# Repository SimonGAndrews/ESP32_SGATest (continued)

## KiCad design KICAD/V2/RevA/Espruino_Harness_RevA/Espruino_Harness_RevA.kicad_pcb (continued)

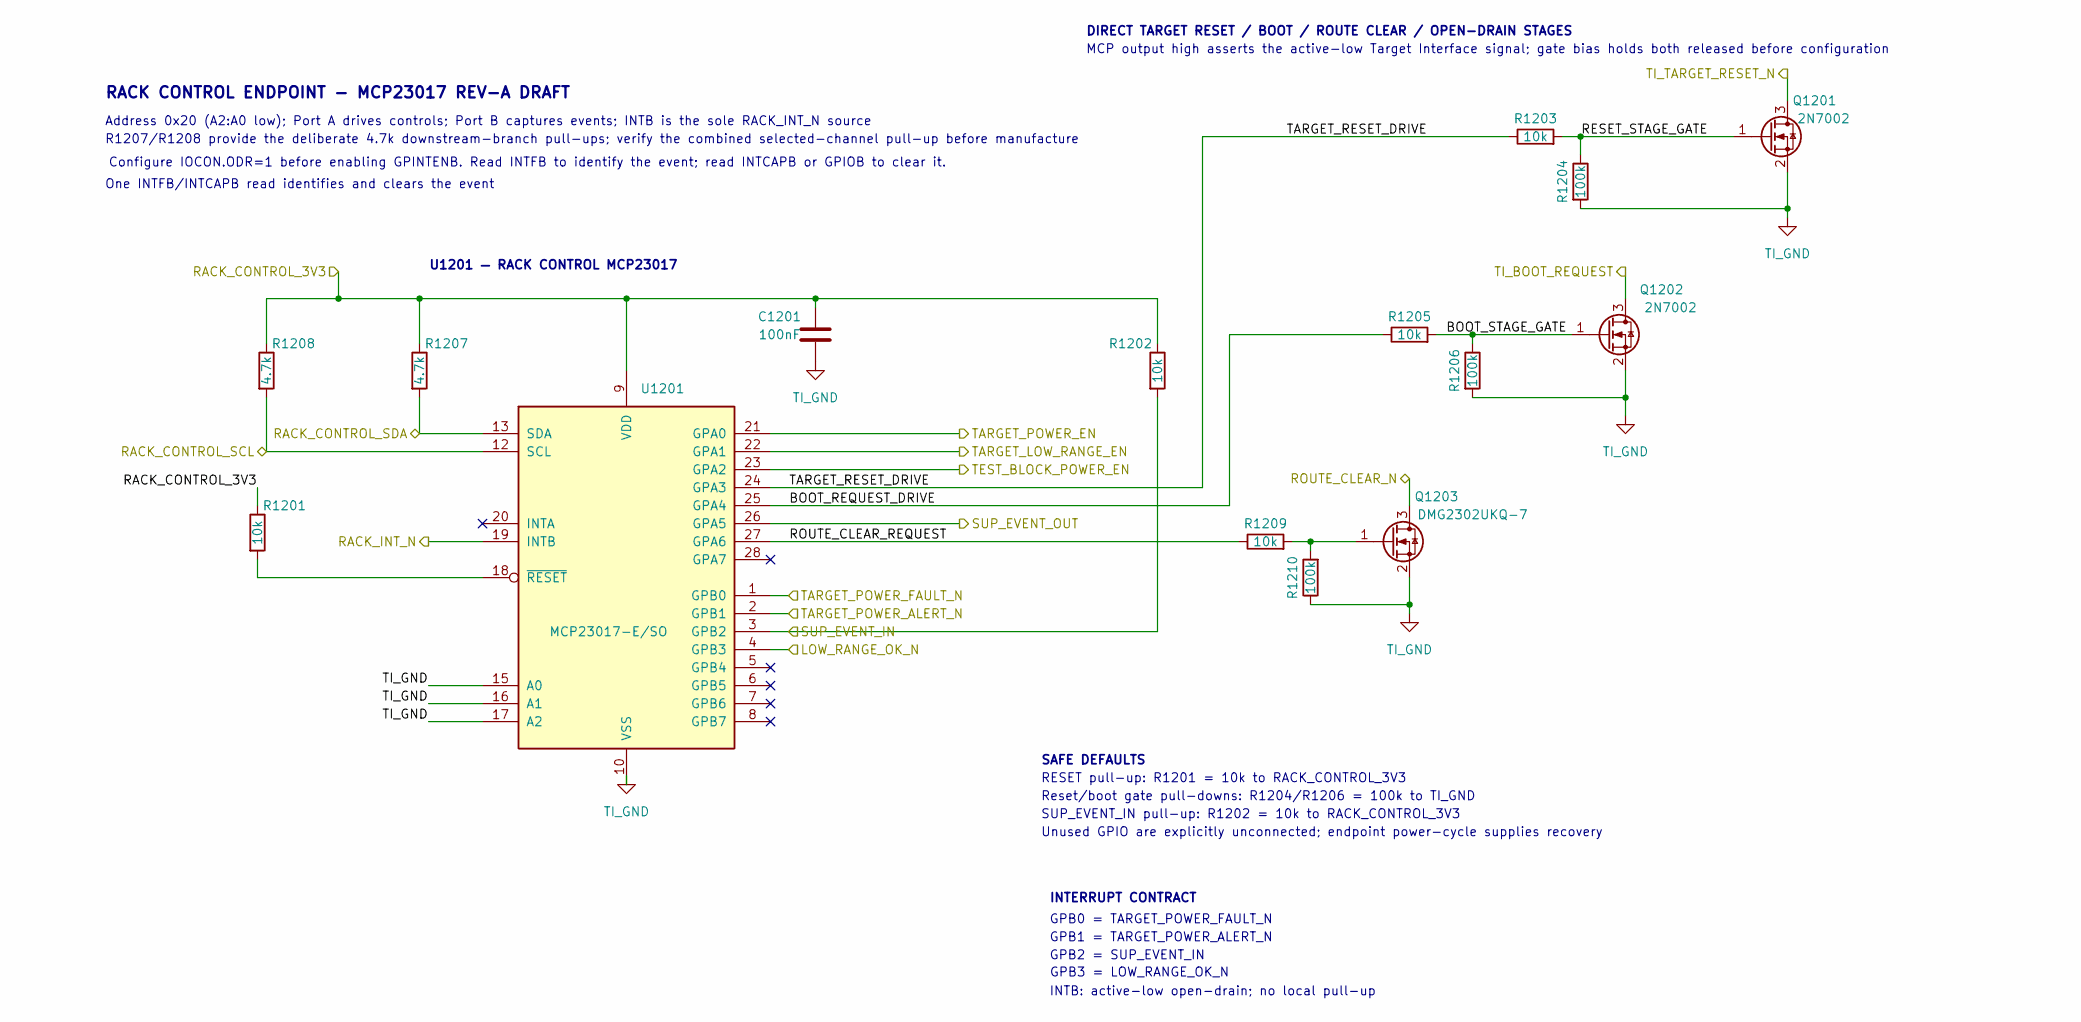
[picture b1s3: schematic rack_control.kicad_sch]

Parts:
C1201: 100nF; C_0603_1608Metric
Q1201, Q1202: 2N7002; SOT-23
Q1203: DMG2302UKQ-7; SOT-23; MPN DMG2302UKQ-7
R1201, R1202, R1203, R1205, R1209: 10k; R_0603_1608Metric
R1204, R1206, R1210: 100k; R_0603_1608Metric
R1207, R1208: 4.7k; R_0603_1608Metric
U1201: MCP23017-E/SO; SOIC-28W_7.5x17.9mm_P1.27mm

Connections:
/LOW_RANGE_OK_N: U1201.4 (GPB3); also elsewhere on the board
/RACK_CONTROL_3V3: C1201.1, R1201.1, R1202.1, R1207.1, R1208.1, U1201.9 (VDD); also elsewhere on the board
/RACK_CONTROL_SCL: R1208.2, U1201.12 (SCL); also elsewhere on the board
/RACK_CONTROL_SDA: R1207.2, U1201.13 (SDA); also elsewhere on the board
/RACK_INT_N: U1201.19 (INTB)
/ROUTE_CLEAR_N: Q1203.3 (D); also elsewhere on the board
/SUP_EVENT_IN: R1202.2, U1201.3 (GPB2); also elsewhere on the board
/SUP_EVENT_OUT: U1201.26 (GPA5); also elsewhere on the board
/TARGET_LOW_RANGE_EN: U1201.22 (GPA1); also elsewhere on the board
/TARGET_POWER_ALERT_N: U1201.2 (GPB1); also elsewhere on the board
/TARGET_POWER_EN: U1201.21 (GPA0); also elsewhere on the board
/TARGET_POWER_FAULT_N: U1201.1 (GPB0); also elsewhere on the board
/TEST_BLOCK_POWER_EN: U1201.23 (GPA2); also elsewhere on the board
/TI_BOOT_REQUEST: Q1202.3 (D); also elsewhere on the board
/TI_TARGET_RESET_N: Q1201.3 (D); also elsewhere on the board
/V2 Rev-A Rack Control Endpoint/BOOT_REQUEST_DRIVE: R1205.1, U1201.25 (GPA4)
/V2 Rev-A Rack Control Endpoint/BOOT_STAGE_GATE: Q1202.1 (G), R1205.2, R1206.1
/V2 Rev-A Rack Control Endpoint/RESET_STAGE_GATE: Q1201.1 (G), R1203.2, R1204.1
/V2 Rev-A Rack Control Endpoint/ROUTE_CLEAR_REQUEST: R1209.1, U1201.27 (GPA6)
/V2 Rev-A Rack Control Endpoint/TARGET_RESET_DRIVE: R1203.1, U1201.24 (GPA3)
unnamed: Q1203.1 (G), R1209.2, R1210.2
unnamed: R1201.2, U1201.18 (~RESET)
TI_GND: C1201.2, Q1201.2 (S), Q1202.2 (S), Q1203.2 (S), R1204.2, R1206.2, R1210.1, U1201.10 (VSS), U1201.15 (A0), U1201.16 (A1), U1201.17 (A2); also elsewhere on the board

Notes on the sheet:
GPB1 = TARGET_POWER_ALERT_N
MCP output high asserts the active-low Target Interface signal; gate bias holds both released before configuration
GPB2 = SUP_EVENT_IN
RACK CONTROL ENDPOINT - MCP23017 REV-A DRAFT
DIRECT TARGET RESET / BOOT / ROUTE CLEAR / OPEN-DRAIN STAGES
One INTFB/INTCAPB read identifies and clears the event
SAFE DEFAULTS
SUP_EVENT_IN pull-up: R1202 = 10k to RACK_CONTROL_3V3
Reset/boot gate pull-downs: R1204/R1206 = 100k to TI_GND
RESET pull-up: R1201 = 10k to RACK_CONTROL_3V3
GPB3 = LOW_RANGE_OK_N
INTB: active-low open-drain; no local pull-up
Unused GPIO are explicitly unconnected; endpoint power-cycle supplies recovery
GPB0 = TARGET_POWER_FAULT_N
Address 0x20 (A2:A0 low); Port A drives controls; Port B captures events; INTB is the sole RACK_INT_N source
R1207/R1208 provide the deliberate 4.7k downstream-branch pull-ups; verify the combined selected-channel pull-up before manufacture
U1201 — RACK CONTROL MCP23017
Configure IOCON.ODR=1 before enabling GPINTENB. Read INTFB to identify the event; read INTCAPB or GPIOB to clear it.
INTERRUPT CONTRACT

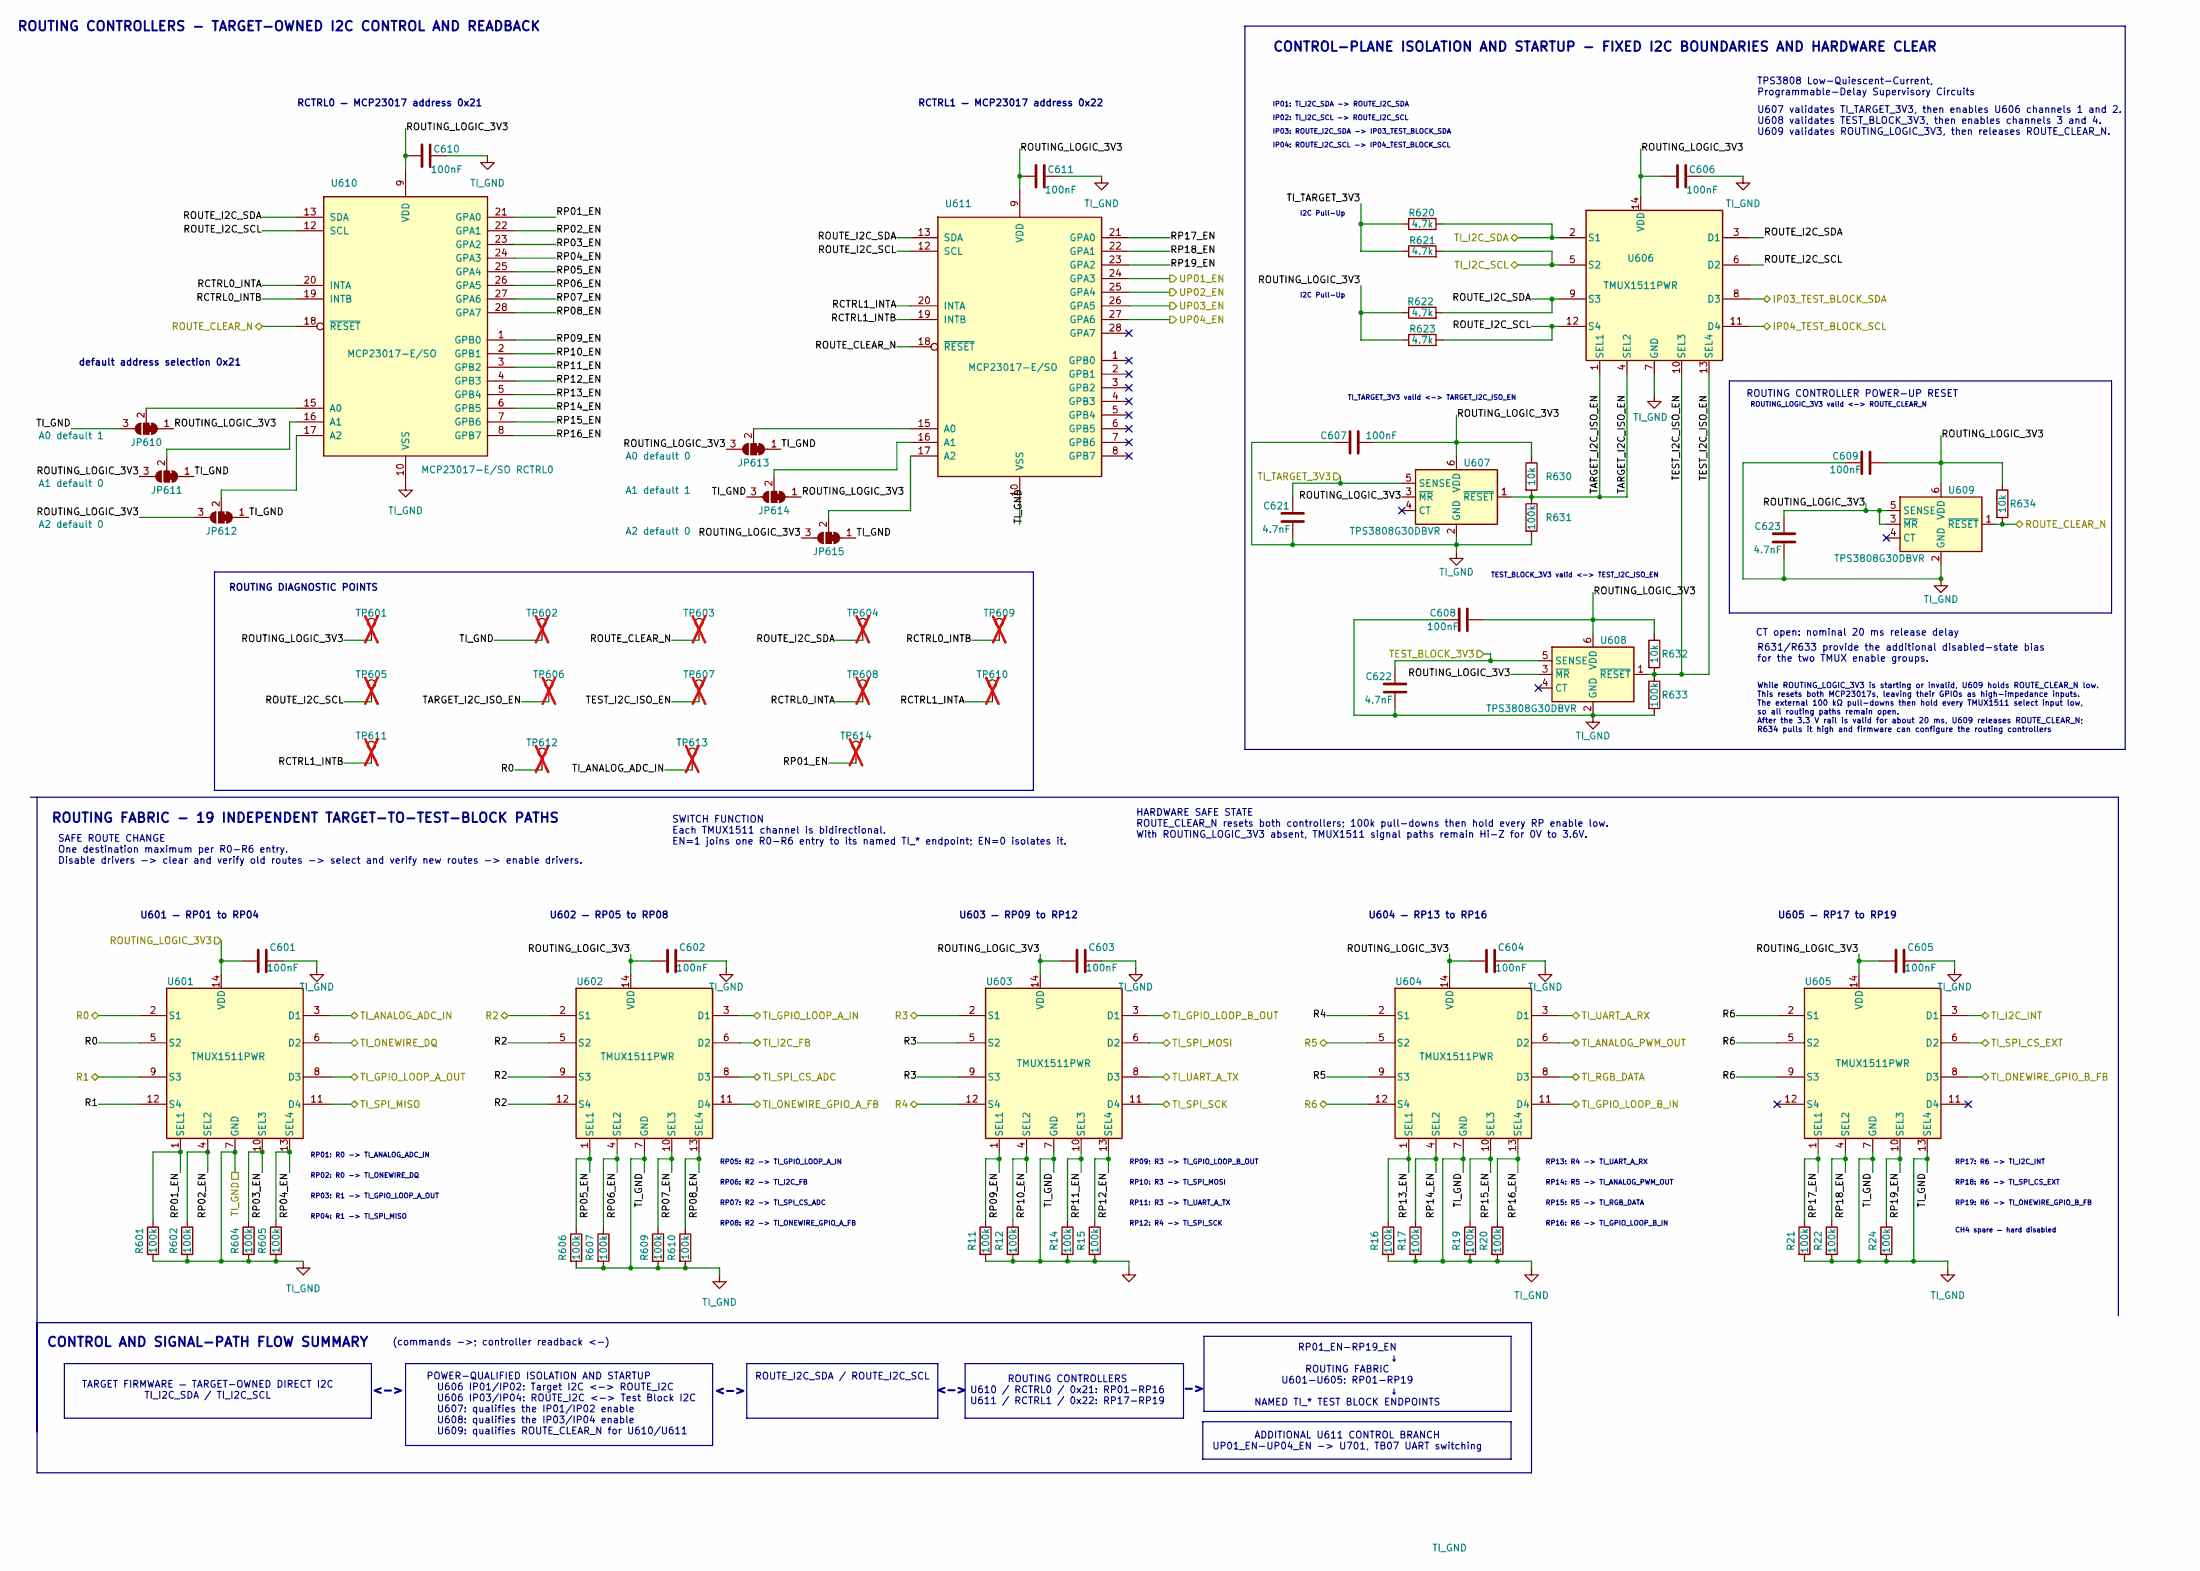
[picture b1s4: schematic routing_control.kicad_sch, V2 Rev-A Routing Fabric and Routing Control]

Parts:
C601, C602, C603, C604, C605, C606, C607, C608, C609, C610, C611: 100nF; C_0603_1608Metric
C621, C622, C623: 4.7nF; C_0603_1608Metric
JP610: A0 default 1; SolderJumper-3_P1.3mm_Bridged12_RoundedPad1.0x1.5mm_NumberL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
JP611: A1 default 0; SolderJumper-3_P1.3mm_Bridged12_RoundedPad1.0x1.5mm_NumberL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
JP612, JP615: A2 default 0; SolderJumper-3_P1.3mm_Bridged12_RoundedPad1.0x1.5mm_NumberL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
JP613: A0 default 0; SolderJumper-3_P1.3mm_Bridged12_RoundedPad1.0x1.5mm_NumberL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
JP614: A1 default 1; SolderJumper-3_P1.3mm_Bridged12_RoundedPad1.0x1.5mm_NumberL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
R11, R12, R14, R15, R16, R17, R19, R20, R21, R22, R24, R601, R602, R604, R605, R606, R607, R609, R610, R631, R633: 100k; R_0603_1608Metric
R620, R621, R622, R623: 4.7k; R_0603_1608Metric
R630, R632, R634: 10k; R_0603_1608Metric
TP601: ROUTING_LOGIC_3V3; PinHeader_1x01_P2.54mm_Vertical; MPN 61300111121; not fitted
TP602: TI_GND; PinHeader_1x01_P2.54mm_Vertical; MPN 61300111121; not fitted
TP603: ROUTE_CLEAR_N; PinHeader_1x01_P2.54mm_Vertical; MPN 61300111121; not fitted
TP604: ROUTE_I2C_SDA; PinHeader_1x01_P2.54mm_Vertical; MPN 61300111121; not fitted
TP605: ROUTE_I2C_SCL; PinHeader_1x01_P2.54mm_Vertical; MPN 61300111121; not fitted
TP606: TARGET_I2C_ISO_EN; PinHeader_1x01_P2.54mm_Vertical; MPN 61300111121; not fitted
TP607: TEST_I2C_ISO_EN; PinHeader_1x01_P2.54mm_Vertical; MPN 61300111121; not fitted
TP608: RCTRL0_INTA; PinHeader_1x01_P2.54mm_Vertical; MPN 61300111121; not fitted
TP609: RCTRL0_INTB; PinHeader_1x01_P2.54mm_Vertical; MPN 61300111121; not fitted
TP610: RCTRL1_INTA; PinHeader_1x01_P2.54mm_Vertical; MPN 61300111121; not fitted
TP611: RCTRL1_INTB; PinHeader_1x01_P2.54mm_Vertical; MPN 61300111121; not fitted
TP612: R0; PinHeader_1x01_P2.54mm_Vertical; MPN 61300111121; not fitted
TP613: TI_ANALOG_ADC_IN; PinHeader_1x01_P2.54mm_Vertical; MPN 61300111121; not fitted
TP614: RP01_EN; PinHeader_1x01_P2.54mm_Vertical; MPN 61300111121; not fitted
U601, U602, U603, U604, U605, U606: TMUX1511; TSSOP-14_4.4x5mm_P0.65mm; MPN TMUX1511PWR
U607, U608, U609: TPS3808G30DBVR; SOT-23-6; MPN TPS3808G30DBVR
U610: MCP23017-E/SO RCTRL0; SOIC-28W_7.5x17.9mm_P1.27mm; MPN MCP23017-E/SO
U611: MCP23017-E/SO RCTRL1; SOIC-28W_7.5x17.9mm_P1.27mm; MPN MCP23017-E/SO

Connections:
/IP03_TEST_BLOCK_SDA: U606.8 (D3); also elsewhere on the board
/IP04_TEST_BLOCK_SCL: U606.11 (D4); also elsewhere on the board
/R0: TP612.1, U601.2 (S1), U601.5 (S2); also elsewhere on the board
/R1: U601.9 (S3), U601.12 (S4); also elsewhere on the board
/R2: U602.2 (S1), U602.5 (S2), U602.9 (S3), U602.12 (S4); also elsewhere on the board
/R3: U603.2 (S1), U603.5 (S2), U603.9 (S3); also elsewhere on the board
/R4: U603.12 (S4), U604.2 (S1); also elsewhere on the board
/R5: U604.5 (S2), U604.9 (S3); also elsewhere on the board
/R6: U604.12 (S4), U605.2 (S1), U605.5 (S2), U605.9 (S3); also elsewhere on the board
/ROUTE_CLEAR_N: R634.2, TP603.1, U609.1 (~RESET), U610.18 (~RESET), U611.18 (~RESET); also elsewhere on the board
/ROUTING_LOGIC_3V3: C601.1, C602.1, C603.1, C604.1, C605.1, C606.1, C607.1, C608.1, C609.1, C610.1, C611.1, C623.1, JP610.1 (A), JP611.3 (B), JP612.3 (B), JP613.3 (B), JP614.1 (A), JP615.3 (B), R622.1, R623.1, R630.1, R632.1, R634.1, TP601.1, U601.14 (VDD), U602.14 (VDD), U603.14 (VDD), U604.14 (VDD), U605.14 (VDD), U606.14 (VDD), U607.3 (~MR), U607.6 (VDD), U608.3 (~MR), U608.6 (VDD), U609.3 (~MR), U609.5 (SENSE), U609.6 (VDD), U610.9 (VDD), U611.9 (VDD); also elsewhere on the board
/Routing_Control/RCTRL0_INTA: TP608.1, U610.20 (INTA)
/Routing_Control/RCTRL0_INTB: TP609.1, U610.19 (INTB)
/Routing_Control/RCTRL1_INTA: TP610.1, U611.20 (INTA)
/Routing_Control/RCTRL1_INTB: TP611.1, U611.19 (INTB)
/Routing_Control/ROUTE_I2C_SCL: R623.2, TP605.1, U606.6 (D2), U606.12 (S4), U610.12 (SCL), U611.12 (SCL)
/Routing_Control/ROUTE_I2C_SDA: R622.2, TP604.1, U606.3 (D1), U606.9 (S3), U610.13 (SDA), U611.13 (SDA)
/Routing_Control/RP01_EN: R601.1, TP614.1, U601.1 (SEL1), U610.21 (GPA0)
/Routing_Control/RP02_EN: R602.1, U601.4 (SEL2), U610.22 (GPA1)
/Routing_Control/RP03_EN: R604.1, U601.10 (SEL3), U610.23 (GPA2)
/Routing_Control/RP04_EN: R605.1, U601.13 (SEL4), U610.24 (GPA3)
/Routing_Control/RP05_EN: R606.1, U602.1 (SEL1), U610.25 (GPA4)
/Routing_Control/RP06_EN: R607.1, U602.4 (SEL2), U610.26 (GPA5)
/Routing_Control/RP07_EN: R609.1, U602.10 (SEL3), U610.27 (GPA6)
/Routing_Control/RP08_EN: R610.1, U602.13 (SEL4), U610.28 (GPA7)
/Routing_Control/RP09_EN: R11.1, U603.1 (SEL1), U610.1 (GPB0)
/Routing_Control/RP10_EN: R12.1, U603.4 (SEL2), U610.2 (GPB1)
/Routing_Control/RP11_EN: R14.1, U603.10 (SEL3), U610.3 (GPB2)
/Routing_Control/RP12_EN: R15.1, U603.13 (SEL4), U610.4 (GPB3)
/Routing_Control/RP13_EN: R16.1, U604.1 (SEL1), U610.5 (GPB4)
/Routing_Control/RP14_EN: R17.1, U604.4 (SEL2), U610.6 (GPB5)
/Routing_Control/RP15_EN: R19.1, U604.10 (SEL3), U610.7 (GPB6)
/Routing_Control/RP16_EN: R20.1, U604.13 (SEL4), U610.8 (GPB7)
/Routing_Control/RP17_EN: R21.1, U605.1 (SEL1), U611.21 (GPA0)
/Routing_Control/RP18_EN: R22.1, U605.4 (SEL2), U611.22 (GPA1)
/Routing_Control/RP19_EN: R24.1, U605.10 (SEL3), U611.23 (GPA2)
/Routing_Control/TARGET_I2C_ISO_EN: R630.2, R631.1, TP606.1, U606.1 (SEL1), U606.4 (SEL2), U607.1 (~RESET)
/Routing_Control/TEST_I2C_ISO_EN: R632.2, R633.1, TP607.1, U606.10 (SEL3), U606.13 (SEL4), U608.1 (~RESET)
/TEST_BLOCK_3V3: C622.1, U608.5 (SENSE); also elsewhere on the board
/TI_ANALOG_ADC_IN: TP613.1, U601.3 (D1); also elsewhere on the board
/TI_ANALOG_PWM_OUT: U604.6 (D2); also elsewhere on the board
/TI_GPIO_LOOP_A_IN: U602.3 (D1); also elsewhere on the board
/TI_GPIO_LOOP_A_OUT: U601.8 (D3); also elsewhere on the board
/TI_GPIO_LOOP_B_IN: U604.11 (D4); also elsewhere on the board
/TI_GPIO_LOOP_B_OUT: U603.3 (D1); also elsewhere on the board
/TI_I2C_FB: U602.6 (D2); also elsewhere on the board
/TI_I2C_INT: U605.3 (D1); also elsewhere on the board
/TI_I2C_SCL: R621.2, U606.5 (S2); also elsewhere on the board
/TI_I2C_SDA: R620.1, U606.2 (S1); also elsewhere on the board
/TI_ONEWIRE_DQ: U601.6 (D2); also elsewhere on the board
/TI_ONEWIRE_GPIO_A_FB: U602.11 (D4); also elsewhere on the board
/TI_ONEWIRE_GPIO_B_FB: U605.8 (D3); also elsewhere on the board
/TI_RGB_DATA: U604.8 (D3); also elsewhere on the board
/TI_SPI_CS_ADC: U602.8 (D3); also elsewhere on the board
/TI_SPI_CS_EXT: U605.6 (D2); also elsewhere on the board
/TI_SPI_MISO: U601.11 (D4); also elsewhere on the board
/TI_SPI_MOSI: U603.6 (D2); also elsewhere on the board
/TI_SPI_SCK: U603.11 (D4); also elsewhere on the board
/TI_TARGET_3V3: C621.1, R620.2, R621.1, U607.5 (SENSE); also elsewhere on the board
/TI_UART_A_RX: U604.3 (D1); also elsewhere on the board
/TI_UART_A_TX: U603.8 (D3); also elsewhere on the board
/UP01_EN: U611.24 (GPA3); also elsewhere on the board
/UP02_EN: U611.25 (GPA4); also elsewhere on the board
/UP03_EN: U611.26 (GPA5); also elsewhere on the board
/UP04_EN: U611.27 (GPA6); also elsewhere on the board
unnamed: JP610.2 (C), U610.15 (A0)
unnamed: JP611.2 (C), U610.16 (A1)
unnamed: JP612.2 (C), U610.17 (A2)
unnamed: JP613.2 (C), U611.15 (A0)
unnamed: JP614.2 (C), U611.16 (A1)
unnamed: JP615.2 (C), U611.17 (A2)
TI_GND: C601.2, C602.2, C603.2, C604.2, C605.2, C606.2, C607.2, C608.2, C609.2, C610.2, C611.2, C621.2, C622.2, C623.2, JP610.3 (B), JP611.1 (A), JP612.1 (A), JP613.1 (A), JP614.3 (B), JP615.1 (A), R11.2, R12.2, R14.2, R15.2, R16.2, R17.2, R19.2, R20.2, R21.2, R22.2, R24.2, R601.2, R602.2, R604.2, R605.2, R606.2, R607.2, R609.2, R610.2, R631.2, R633.2, TP602.1, U601.7 (GND), U602.7 (GND), U603.7 (GND), U604.7 (GND), U605.7 (GND), U605.13 (SEL4), U606.7 (GND), U607.2 (GND), U608.2 (GND), U609.2 (GND), U610.10 (VSS), U611.10 (VSS); also elsewhere on the board

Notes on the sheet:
<->
U607 validates TI_TARGET_3V3, then enables U606 channels 1 and 2. U608 validates TEST_BLOCK_3V3, then enables channels 3 and 4. U609 validates ROUTING_LOGIC_3V3, then releases ROUTE_CLEAR_N.
RP08: R2 -> TI_ONEWIRE_GPIO_A_FB
RP01_EN-RP19_EN ↓ ROUTING FABRIC U601-U605: RP01-RP19 ↓ NAMED TI_* TEST BLOCK ENDPOINTS ADDITIONAL U611 CONTROL BRANCH UP01_EN-UP04_EN -> U701, TB07 UART switching
ROUTING DIAGNOSTIC POINTS
CONTROL AND SIGNAL-PATH FLOW SUMMARY
IP04: ROUTE_I2C_SCL -> IP04_TEST_BLOCK_SCL
default address selection 0x21
RCTRL0 — MCP23017 address 0x21
RP10: R3 -> TI_SPI_MOSI
ROUTING_LOGIC_3V3 valid <-> ROUTE_CLEAR_N
RP09: R3 -> TI_GPIO_LOOP_B_OUT
RCTRL1 — MCP23017 address 0x22
RP01: R0 -> TI_ANALOG_ADC_IN
U603 — RP09 to RP12
RP06: R2 -> TI_I2C_FB
RP16: R6 -> TI_GPIO_LOOP_B_IN
(commands ->; controller readback <-)
TPS3808 Low-Quiescent-Current, Programmable-Delay Supervisory Circuits
CT open: nominal 20 ms release delay
IP01: TI_I2C_SDA -> ROUTE_I2C_SDA
U602 — RP05 to RP08
IP03: ROUTE_I2C_SDA -> IP03_TEST_BLOCK_SDA
POWER-QUALIFIED ISOLATION AND STARTUP U606 IP01/IP02: Target I2C <-> ROUTE_I2C U606 IP03/IP04: ROUTE_I2C <-> Test Block I2C U607: qualifies the IP01/IP02 enable U608: qualifies the IP03/IP04 enable U609: qualifies ROUTE_CLEAR_N for U610/U611
RP19: R6 -> TI_ONEWIRE_GPIO_B_FB
RP02: R0 -> TI_ONEWIRE_DQ
ROUTE_I2C_SDA / ROUTE_I2C_SCL
I2C Pull-Up
RP15: R5 -> TI_RGB_DATA
RP04: R1 -> TI_SPI_MISO
RP03: R1 -> TI_GPIO_LOOP_A_OUT
HARDWARE SAFE STATE ROUTE_CLEAR_N resets both controllers; 100k pull-downs then hold every RP enable low. With ROUTING_LOGIC_3V3 absent, TMUX1511 signal paths remain Hi-Z for 0V to 3.6V.
RP12: R4 -> TI_SPI_SCK
TEST_BLOCK_3V3 valid <-> TEST_I2C_ISO_EN
U605 — RP17 to RP19
RP11: R3 -> TI_UART_A_TX
RP07: R2 -> TI_SPI_CS_ADC
RP05: R2 -> TI_GPIO_LOOP_A_IN
CONTROL-PLANE ISOLATION AND STARTUP - FIXED I2C BOUNDARIES AND HARDWARE CLEAR
RP17: R6 -> TI_I2C_INT
